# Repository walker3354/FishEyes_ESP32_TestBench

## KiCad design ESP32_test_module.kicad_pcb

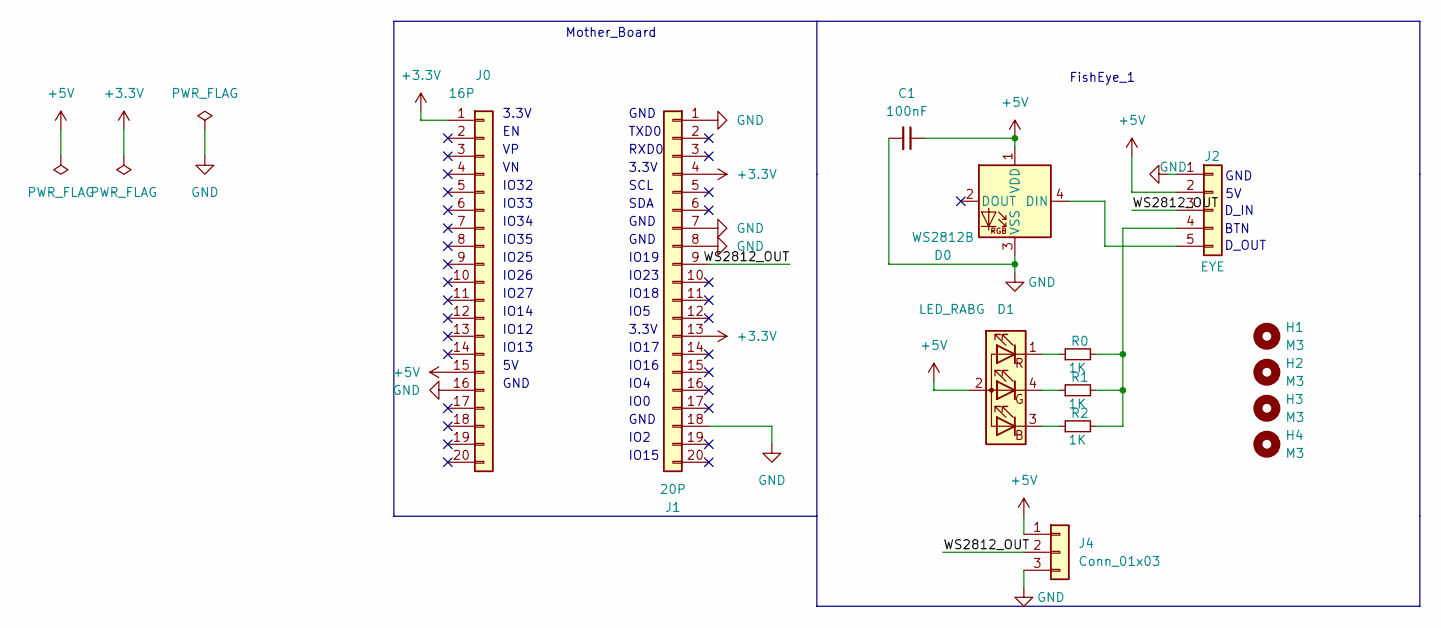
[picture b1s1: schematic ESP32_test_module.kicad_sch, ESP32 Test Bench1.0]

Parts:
C1: 100nF; C_0603_1608Metric
D0: WS2812B; LED_WS2812B_PLCC4_5.0x5.0mm_P3.2mm
D1: LED_RABG; LED_Kingbright_AAA3528ESGCT
H1, H2, H3, H4: M3; MountingHole_3.2mm_M3
J0: 16P; PinSocket_1x20_P2.54mm_Vertical
J1: 20P; PinSocket_1x20_P2.54mm_Vertical
J2: EYE; JST_SH_BM05B-SRSS-TB_1x05-1MP_P1.00mm_Vertical
J4: Conn_01x03; JST_SH_BM03B-SRSS-TB_1x03-1MP_P1.00mm_Vertical
R0, R1, R2: 1K; R_0603_1608Metric

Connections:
+3.3V: J0.1, J1.4, J1.13
+5V: C1.1, D0.1 (VDD), D1.2 (A), J0.15, J2.2, J4.1
/WS2812_OUT: J1.9, J2.3, J4.2
GND: C1.2, D0.3 (VSS), J0.16, J1.1, J1.7, J1.8, J1.18, J2.1, J4.3
unnamed: J2.4, R0.2, R1.2, R2.2
unnamed: D0.4 (DIN), J2.5
unnamed: D1.1 (RK), R0.1
unnamed: D1.4 (GK), R1.1
unnamed: D1.3 (BK), R2.1

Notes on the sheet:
Mother_Board
GND
IO18
IO23
TXD0
D_IN
IO17
IO33
D_OUT
BTN
IO0
IO14
IO27
IO15
3.3V
IO2
IO19
SDA
IO32
FishEye_1
IO35
IO5
RXD0
IO34
IO4
IO13
SCL
IO12
IO16
IO26
IO25

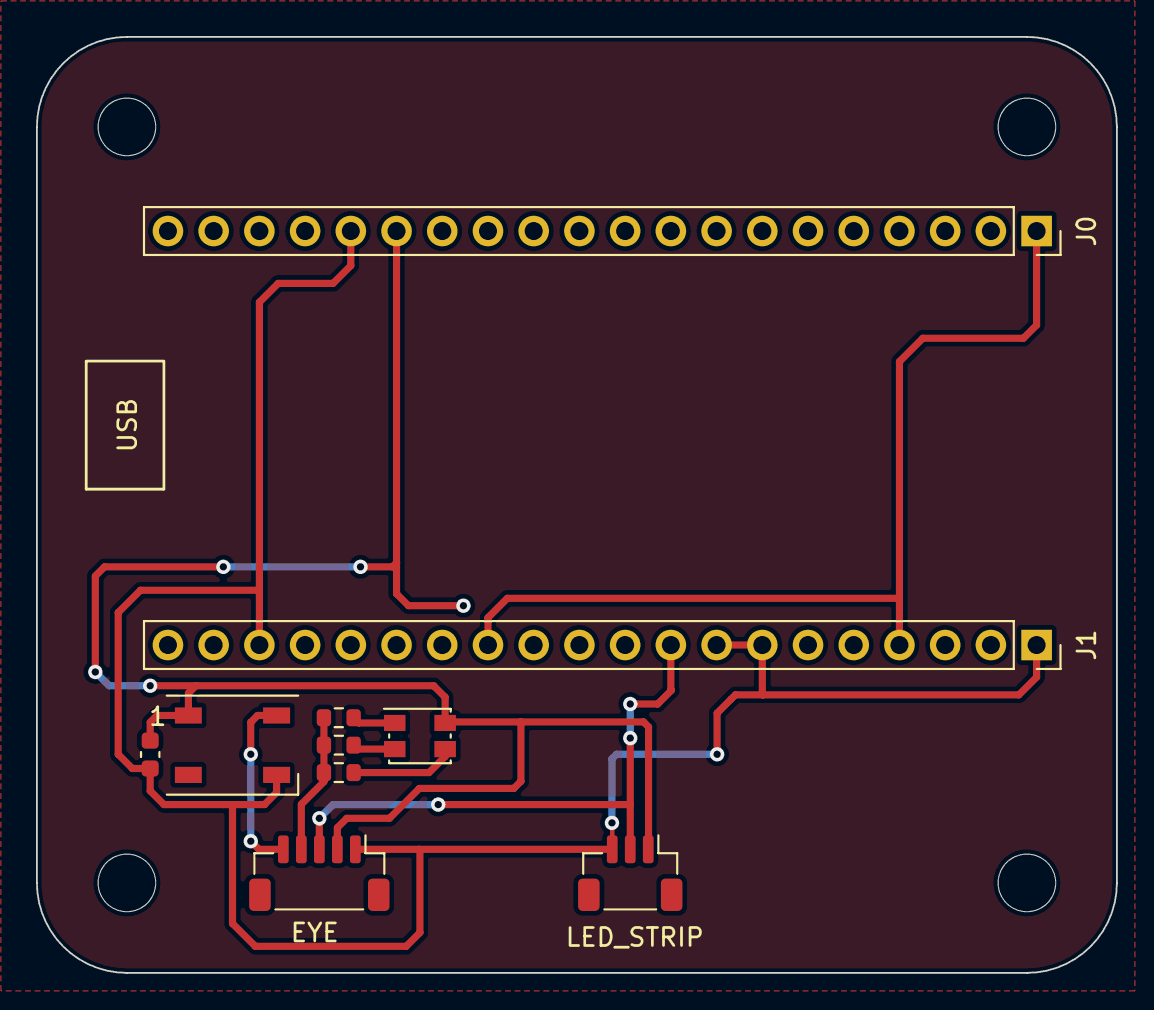
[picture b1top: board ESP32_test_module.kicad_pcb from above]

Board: 2 copper layers, 60.0 x 52.0 mm, 14 parts (0 on the bottom side), 9 nets.

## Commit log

2023-08-11 version 1.0
